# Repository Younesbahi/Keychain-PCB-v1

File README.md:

# Keychain-PCB-v1

This project is a simple USB powered PCB keychain that lights up when plugged into a computer. It has zaero storage or data. The goal of this V1 was to learn the basics of USB power, schematics, and PCB layout without adding unnecessary complexity (im a bit rusty) 

The board uses USB 5V to power an LED through a resistor. The USB data lines are left unconnected on purpose. The keychain is meant to hang on my large, annoying set of keys and includes my personalized information on the back. If I ever lose them, whoever finds them knows who to return them to.

## BOM
| Item       | Description             | Quantity | Unit Price ($) | Total Price ($) | URL                                                                 | Running Total ($ w/ Tax) | Total w/ Shipping ($) |
|------------|-------------------------|----------|----------------|-----------------|----------------------------------------------------------------------|---------------------------|------------------------|
| C130115    | White SMD LED 0805      | 5        | 0.03           | 0.16            | https://www.lcsc.com/product-detail/C130115.html                     | 0.18                      | 16.78                  |
| C2076063   | 1 kΩ Resistor 0603      | 5        | 0.52           | 2.60            | https://www.lcsc.com/product-detail/C2076063.html                    | 2.94                      |                        |
| PCB        | PCB Manufacturing       | 5        | 0.44           | 2.20            | https://jlcpcb.com/                                                  | 2.49                      | 8.10                   |
| **Total**  |                         |          |                |                 |                                                                      |                           | **24.88**              |

### Rendered PCB

### Schematic

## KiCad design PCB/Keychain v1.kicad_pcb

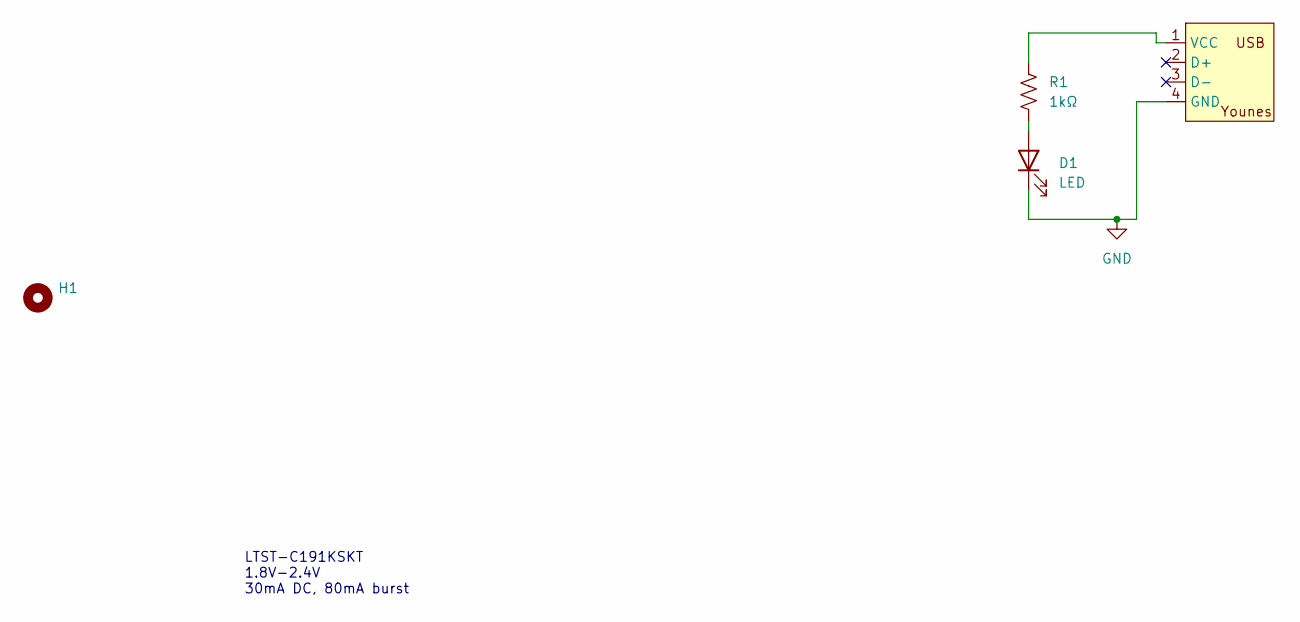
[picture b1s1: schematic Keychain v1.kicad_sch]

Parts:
D1: LED; LED_0805_2012Metric_Pad1.15x1.40mm_HandSolder
H1: MountingHole; MountingHole_2.1mm
R1: 1kΩ; R_0603_1608Metric
U1: Untitled

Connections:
GND: D1.1 (K), U1.4 (GND)
unnamed: D1.2 (A), R1.2
unnamed: R1.1, U1.1 (VCC)

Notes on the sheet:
LTST-C191KSKT 1.8V-2.4V 30mA DC, 80mA burst

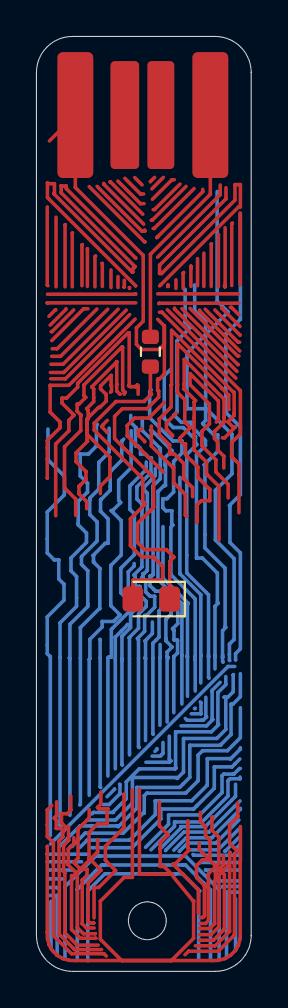
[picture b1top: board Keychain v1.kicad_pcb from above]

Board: 2 copper layers, 11.9 x 51.9 mm, 4 parts (0 on the bottom side), 3 nets.

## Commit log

2025-12-16 Create
2025-12-16 Create pcb
